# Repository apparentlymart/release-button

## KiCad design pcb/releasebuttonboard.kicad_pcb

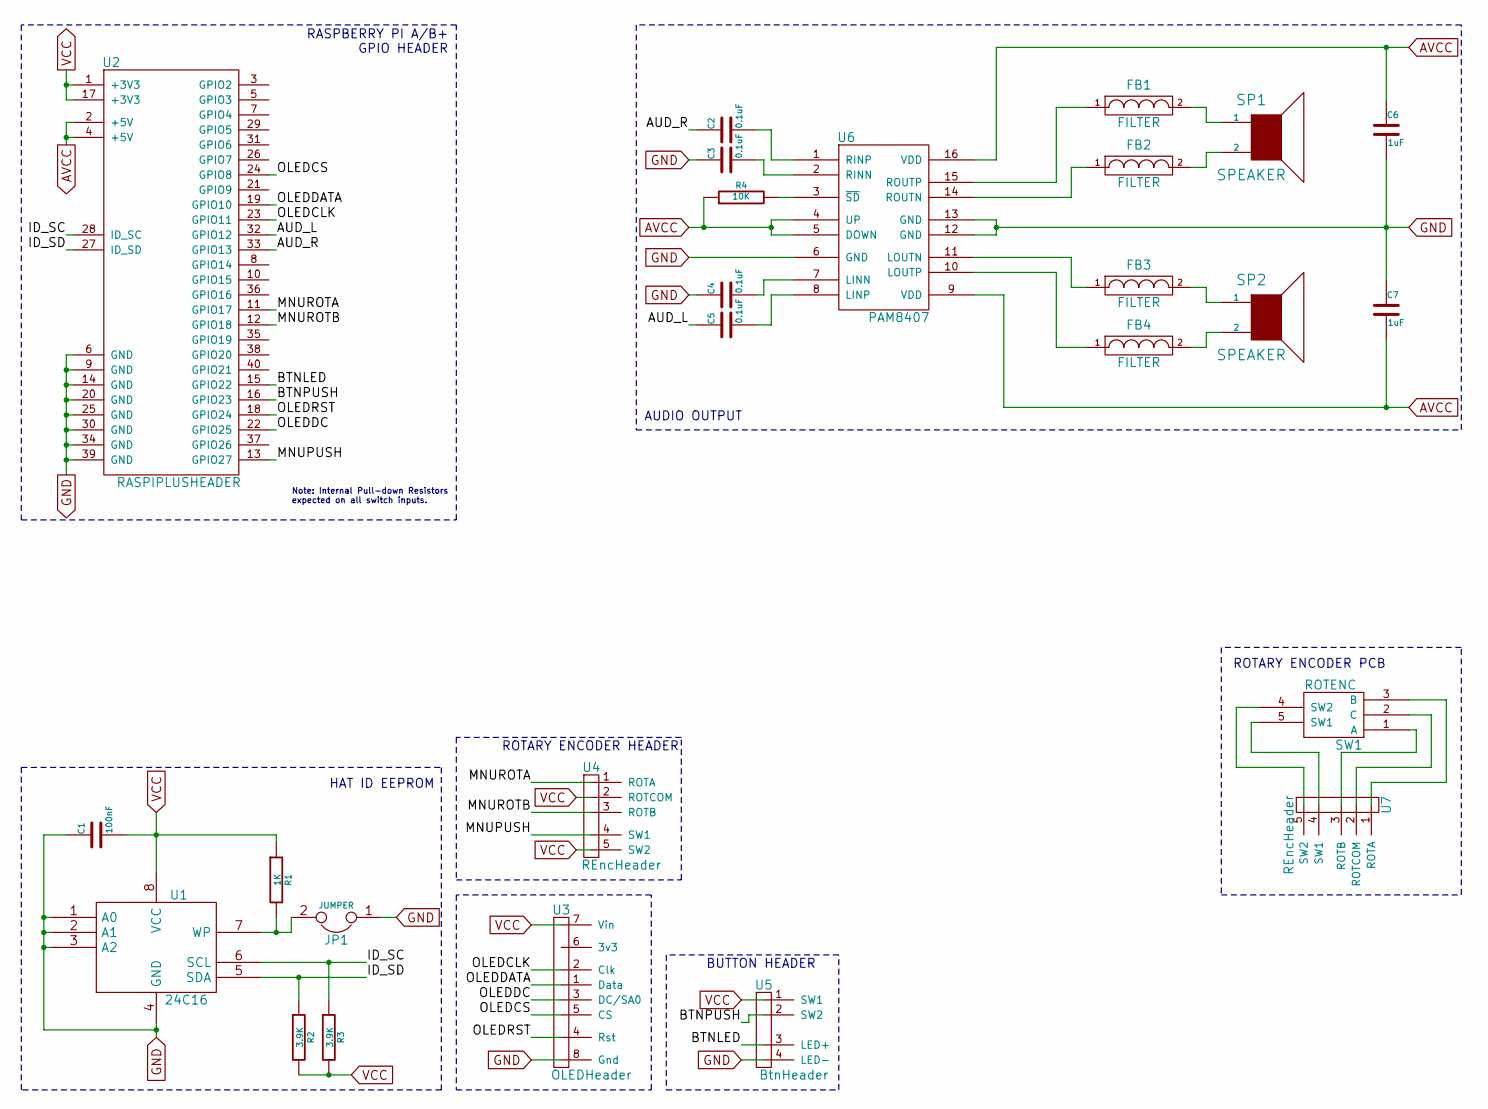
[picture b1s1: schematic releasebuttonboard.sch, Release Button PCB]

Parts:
C1: 100nF
C2, C3, C4, C5: 0.1uF
C6, C7: 1uF
FB1, FB2, FB3, FB4: FILTER
JP1: JUMPER
R1: 1K
R2, R3: 3.9K
R4: 10K
SP1, SP2: SPEAKER
SW1: ROTENC
U1: 24C16
U2: RASPIPLUSHEADER
U3: OLEDHeader
U4, U7: REncHeader
U5: BtnHeader
U6: PAM8407

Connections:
/AUD_L: C5.1, U2.32 (GPIO12)
/AUD_R: C2.1, U2.33 (GPIO13)
/BTNLED: U2.15 (GPIO22), U5.3 (LED+)
/BTNPUSH: U2.16 (GPIO23), U5.2 (SW2)
/ID_SC: R3.1, U1.6 (SCL), U2.28 (ID_SC)
/ID_SD: R2.1, U1.5 (SDA), U2.27 (ID_SD)
/MNUPUSH: U2.13 (GPIO27), U4.4 (SW1)
/MNUROTA: U2.11 (GPIO17), U4.1 (ROTA)
/MNUROTB: U2.12 (GPIO18), U4.3 (ROTB)
/OLEDCLK: U2.23 (GPIO11), U3.2 (Clk)
/OLEDCS: U2.24 (GPIO8), U3.5 (CS)
/OLEDDATA: U2.19 (GPIO10), U3.1 (Data)
/OLEDDC: U2.22 (GPIO25), U3.3 (DC/SA0)
/OLEDRST: U2.18 (GPIO24), U3.4 (Rst)
AVCC: C6.1, C7.2, R4.1, U2.2 (+5V), U2.4 (+5V), U6.4 (UP), U6.5 (DOWN), U6.9 (VDD), U6.16 (VDD)
GND: C1.1, C3.1, C4.1, C6.2, C7.1, JP1.1, U1.1 (A0), U1.2 (A1), U1.3 (A2), U1.4 (GND), U2.6 (GND), U2.9 (GND), U2.14 (GND), U2.20 (GND), U2.25 (GND), U2.30 (GND), U2.34 (GND), U2.39 (GND), U3.8 (Gnd), U5.4 (LED-), U6.6 (GND), U6.12 (GND), U6.13 (GND)
unnamed: C2.2, U6.1 (RINP)
unnamed: C3.2, U6.2 (RINN)
unnamed: C4.2, U6.7 (LINN)
unnamed: C5.2, U6.8 (LINP)
unnamed: FB1.1, U6.15 (ROUTP)
unnamed: FB1.2, SP1.1
unnamed: FB2.1, U6.14 (ROUTN)
unnamed: FB2.2, SP1.2
unnamed: FB3.1, U6.11 (LOUTN)
unnamed: FB3.2, SP2.1
unnamed: FB4.1, U6.10 (LOUTP)
unnamed: FB4.2, SP2.2
unnamed: JP1.2, R1.2, U1.7 (WP)
unnamed: R4.2, U6.3 (~SD)
unnamed: SW1.1 (A), U7.3 (ROTB)
unnamed: SW1.2 (C), U7.2 (ROTCOM)
unnamed: SW1.3 (B), U7.1 (ROTA)
unnamed: SW1.4 (SW2), U7.5 (SW2)
unnamed: SW1.5 (SW1), U7.4 (SW1)
VCC: C1.2, R1.1, R2.2, R3.2, U1.8 (VCC), U2.1 (+3V3), U2.17 (+3V3), U3.7 (Vin), U4.2 (ROTCOM), U4.5 (SW2), U5.1 (SW1)

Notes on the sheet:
HAT ID EEPROM
AUDIO OUTPUT
Note: Internal Pull-down Resistors expected on all switch inputs.
ROTARY ENCODER HEADER
BUTTON HEADER
RASPBERRY PI A/B+ GPIO HEADER
ROTARY ENCODER PCB

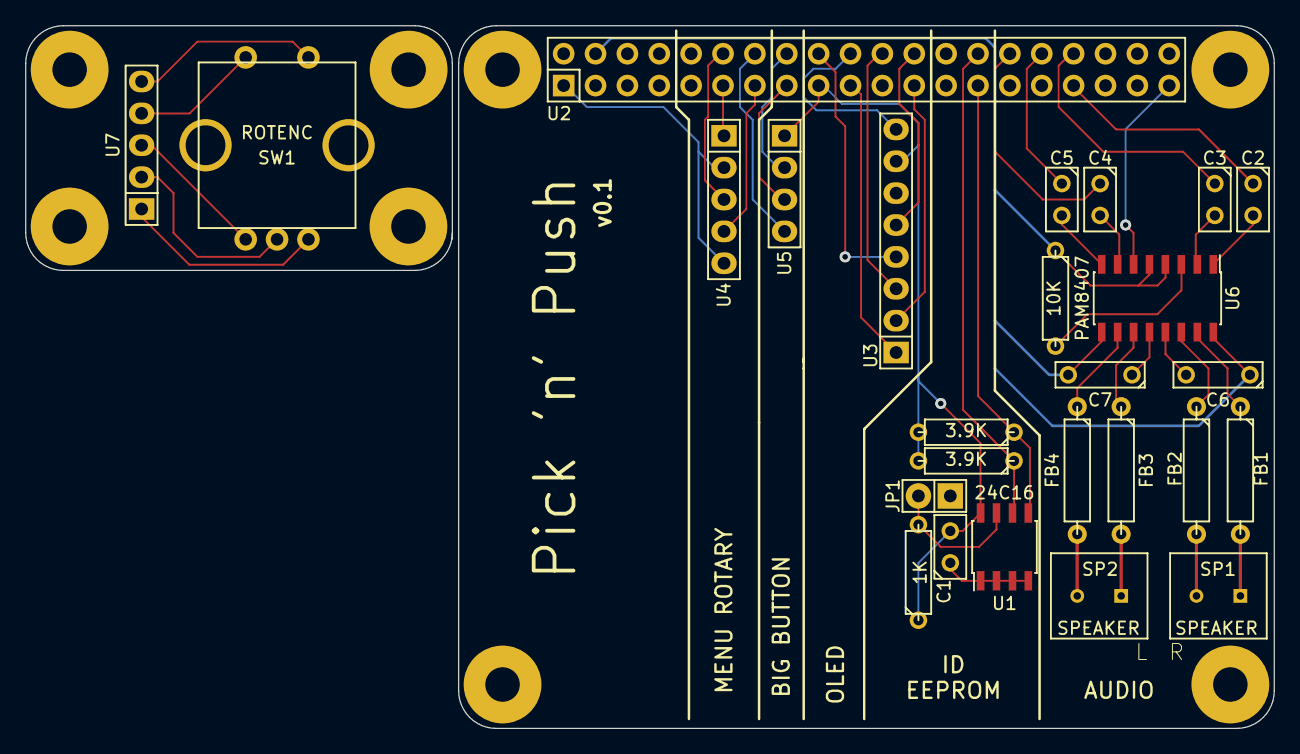
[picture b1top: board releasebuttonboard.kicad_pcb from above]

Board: 4 copper layers, 99.5 x 56.0 mm, 34 parts (0 on the bottom side), 36 nets.

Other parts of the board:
Mounting_Hole_2.75mm, Mounting_Hole_2.75mm#2, Mounting_Hole_2.75mm#3, Mounting_Hole_2.75mm#4, Mounting_Hole_2.75mm#5, Mounting_Hole_2.75mm#6, Mounting_Hole_2.75mm#7, Mounting_Hole_2.75mm#8: VAL**; Mounting_Hole_2.75mm

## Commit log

2014-10-08 initial import
2014-11-06 Simple Makefile
2014-11-06 Add run target to makefile
2014-11-06 progress
2014-12-17 Basic infrastructure for rotary encoder.
2014-12-28 Quick, hacky experiment with rotary encoder.
    Reading a cheap rotary encoder successfully was a bit of an uphill battle
    but this program shows how it can be done in isolation. Something like
    this will eventually be incorporated into the main program.
2014-12-29 Start of modeling the enclosure with OpenSCAD.
    So far we have a model of the enclosure itself (which is a product from
    Polycase) and a model of what turned out to be the wrong size of button.
    There's also an overly-detailed STL model of the Raspberry Pi A+ in there
    which we'll probably later replace with a simpler model that's more
    amenable to CSG operations.
2014-12-30 Model the lid of the enclosure along with the base.
2014-12-30 Overview model with the button in place on the lid.
2015-01-01 Center the model about the origin.
    Everything else is simpler this way.
2015-01-01 Add the OLED and its breakout into the enclosure model.
2015-01-01 Use a beveled edge around the display cutout.
    Not sure yet if Polycase can accommodate this with their CNC process so
    right now this is just aspirational and may get reverted if they can't
    support it.
2015-01-01 Improve the accuracy of the OLED screen module.
    The physical dimensions are derived from the EagleCAD board file released
    by Adafruit, which gives enough information to model the physical outline
    somewhat accurately.
    The updated screen cutout rectangle is derived from the viewing window used
    in Adafruit's "Toaster Mac" 3D printer project.
2015-01-01 Add tolerances to the cutouts.
2015-01-01 Tiny adjustment to display cutout position.
    The display isn't quite centered on the module, but it's totally marginal
    and this difference is smaller than the cut tolerance, so this is really
    just for the sake of completeness.
2015-01-01 Rotary encoder base.
    No knob or nut yet.
2015-01-01 Add a hollow for the rotary encoder screw.
    The screw thread on the rotary encoder is too shallow to make it all the
    way through the top wall of the case, so this indent should allow it to
    screw down enough to stay fastened.
2015-01-01 Add rotary encoder knob.
2015-01-01 Add a straight lip on the screen cutout bevel.
    Cutting to a sharp edge is unlikely to work well, so we'll give a little
    bit of straight lip to avoid cutting the top wall too thin.
2015-01-01 Add a bevel to the hollow for the rotary encoder.
2015-01-03 KiCad project for PCB plus a library of schematics for the headers.
2015-01-03 Drop in the main components to the schematic.
    Not laid out or wired together yet.
2015-01-03 Schematic of ID EEPROM subcircuit.
    (And some extra bits that crept in.)
2015-01-03 Some notes about components for audio output.
2015-01-03 Finish the ID EEPROM circuit.
    Previously we were missing the necessary IO pin pullups and a decoupling
    capacitor.
2015-01-04 PAM8407 schematic symbol.
2015-01-04 Apparently KiCad wants component names in uppercase.
2015-01-04 Audio output circuit.
2015-01-04 Connect OLED header to Raspberry Pi IO pins.
2015-01-04 Rotary encoder header connections.
2015-01-04 Header for big button.
    (Plus misc schematic layout changes.)
2015-01-04 Component annotation.
2015-01-04 Remove unused AVCC label.
2015-01-04 Rotary encoder schematic symbol.
2015-01-04 Schematic for extra rotary encoder PCB.
2015-01-04 More schematic annotation.
2015-01-04 Fix rotary encoder header schematic reference.
    It seems that the case sensitivity rules change when moving between KiCad
    versions.
2015-01-04 Custom PCB footprint library.
2015-01-04 Component to footprint mapping.
2015-01-04 PiHat PCB outline and mounting holes.
2015-01-04 Fix missing connection between ferrite and speaker terminal.
2015-01-04 Initial component layout for the audio part of the PCB.
2015-01-04 Add separate ground pours for analog and digital.
2015-01-04 Route the analog part of the PCB.
2015-01-04 Starting to lay out the EEPROM curcuit and unamped audio.
2015-01-04 Further PCB traces and tweaks.
2015-01-04 Rearrange RaspPi pin assignments for more convenient routing.
    Some of the functions were too spread out on the physical header before.
    Now they are arranged into non-overlapping columns so the board can be
    more conveniently split into several distinct functions.
2015-01-04 Update PCB for new netlist.
2015-01-04 Power the audio amp from the 5V supply.
    This should keep it a little more isolated from the digital supply as well
    as making it easier to route the power tracks.
2015-01-05 New vertical layout of the audio circuit.
    Easier to fit everything in this way and provide clear ground return paths,
    I hope. (Remains to be seen whether the traces will work out.)
2015-01-05 Track routing for the audio portion of the PCB.
2015-01-05 Add dummy copper layer to fake out signal connections on header pin.
    In order for the DRC to consider the routing to be complete it needs to
    know that the GND, VCC and AVCC pins (respectively) on the Raspberry Pi
    header will be connected by the Pi board itself and thus don't need to
    actually be connected on this board. We achieve this by providing a dummy
    copper layer that won't be included in the fab order.
2015-01-05 Use a bigger ground plane in the audio area.
    This expanded plane also includes the power supply tracks.
2015-01-05 Component placement for ID EEPROM region.
2015-01-05 Traces for ID EEPROM circuit portion.
2015-01-05 OLED header placement and routing.
2015-01-05 Connect the ID EEPROM data pins.
2015-01-05 Button and rotary encoder header placement and tracks.
2015-01-05 Place the board title text.
2015-01-05 Add a redundant track to help kicad see a connection.
    KiCad isn't seeing the connection between the via and the ground plane,
    so an extra copper trace line inside the ground plane completes the net.
2015-01-05 Tweak position of version number label.
2015-01-05 Separate rotary encoder PCB.
2015-01-05 Move AVCC trace away from the board edge.
    As it was, it risked being damaged by board outline cutting during
    manufacture.
